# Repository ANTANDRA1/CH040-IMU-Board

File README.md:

ПЛАТА ДЛЯ IMU CH040

ОПИС ПРОЄКТУ

Проєкт являє собою односторонню друковану плату для підключення інерціального модуля CH040 IMU/VRU.

Плата розроблена в KiCad 10.

Основні завдання плати:

- встановлення модуля CH040;
- виведення всіх 18 контактів CH040 на гребінки Dupont з кроком 2.54 мм;
- додаткове виведення робочих інформаційних сигналів на роз'єм JST GH з кроком 1.25 мм;
- забезпечення живлення модуля;
- захист лінії живлення;
- монтажні отвори під гвинти М2.

CH040

CH040 — інерціальний модуль IMU/VRU.

Модуль підтримує UART та CAN-інтерфейси.

Для використання повноцінної CAN-шини необхідний зовнішній CAN-трансивер, оскільки CAN_TX та CAN_RX є логічними сигналами модуля, а не безпосередньо CANH та CANL.

Габарити модуля:

25 × 20 × 2.7 мм

РОЗ'ЄМ J1 — DUPONT 1×9, 2.54 ММ

1 — VDD
2 — GND
3 — EN
4 — IO1
5 — IO2
6 — RXD2
7 — TXD2
8 — GND
9 — IO5

РОЗ'ЄМ J2 — DUPONT 1×9, 2.54 ММ

1 — NRST
2 — RXD3
3 — TXD3
4 — CAN_TX
5 — CAN_RX
6 — IO9
7 — RXD1
8 — TXD1
9 — IO6

Таким чином, на J1 та J2 виведені всі 18 контактів CH040.

РОЗ'ЄМ J3 — JST GH 1×10, 1.25 ММ

На роз'єм J3 виведені робочі інформаційні та керуючі сигнали.

1 — EN
2 — IO1_EXT
3 — IO2_EXT
4 — IO5
5 — IO6
6 — UART1_TX
7 — UART1_RX
8 — CAN_TX
9 — CAN_RX
10 — NRST_EXT

Лінії IO1, IO2, TXD1, RXD1 та NRST підключені до J3 через послідовні резистори 1 кОм.

Контакти RXD2, TXD2, RXD3 та TXD3 не використовуються в поточній конфігурації CH040, а IO9 є зарезервованим, тому вони не дублюються на JST.

ЖИВЛЕННЯ

Живлення плати подається через роз'єм J4.

Робоча напруга:

3.3–5 В

Для захисту лінії живлення використані:

F1 — запобіжник 300 мА
D1 — TVS-діод SMF5.0CA

Схема живлення:

J4 → F1 → VDD → CH040

TVS-діод D1 підключений між VDD та GND.

ПЕРЕМИЧКА GND

Плата виконана односторонньою.

Контакт 8 модуля CH040 є контактом GND.

Через особливості одностороннього трасування його підключення до основної землі виконується через перемичку:

R6 — 0 Ом

Використовується вивідний THT-резистор, який фізично виконує функцію перемички над сигнальними доріжками.

ПОСАДКОВЕ МІСЦЕ CH040

Посадкове місце CH040 створене вручну відповідно до документації виробника.

Основні параметри:

габарит модуля — 25 × 20 мм
розмір контактної площадки — 1.4 × 1.2 мм
основний крок контактів — 2 мм

Під модулем створена спеціальна Keepout-зона.

У цій зоні заборонено:

- прокладати доріжки;
- розміщувати перехідні отвори;
- виконувати заливку міддю.

МОНТАЖ

На платі передбачено чотири монтажні отвори:

H1
H2
H3
H4

Отвори призначені для кріплення плати гвинтами М2.

ОСНОВНІ КОМПОНЕНТИ

U1 — CH040

J1, J2 — Dupont 1×9, 2.54 мм

J3 — JST GH 1×10, 1.25 мм

J4 — роз'єм живлення

R1–R5 — 1 кОм, корпус 0402

R6 — 0 Ом, THT

F1 — 300 мА

D1 — SMF5.0CA

H1–H4 — монтажні отвори М2

СТРУКТУРА ПРОЄКТУ

CH040

KiCad
    Ch040.kicad_pro
    Ch040.kicad_sch
    Ch040.kicad_pcb
    бібліотека символу CH040
    бібліотека посадкового місця CH040

Gerber & Drill
    Gerber-файли
    Drill-файли

Datasheet
    документація CH040

README.txt

ВІДТВОРЕННЯ ПРОЄКТУ

Для відкриття та редагування проєкту рекомендується використовувати KiCad 10.

1. Завантажити або клонувати репозиторій.

2. Відкрити файл Ch040.kicad_pro.

3. Перевірити підключення бібліотеки символу CH040 та бібліотеки його посадкового місця.

4. Відкрити принципову схему.

5. Відкрити PCB.

6. Запустити ERC для перевірки електричної схеми.

7. Запустити DRC для перевірки друкованої плати.

8. Для виробництва використовувати Gerber та Drill-файли з відповідної папки.

ПЕРЕВІРКА ПЛАТИ

Перед формуванням виробничих файлів виконано:

- ERC;
- DRC;
- перевірку нез'єднаних мереж;
- перевірку Keepout-зони CH040;
- перевірку плати у 3D Viewer;
- формування Gerber-файлів;
- формування Drill-файлів.

ПРИМІТКА

Проєкт виконаний відповідно до технічного завдання на розробку плати для IMU CH040.

Репозиторій містить принципову схему, PCB, користувацькі бібліотеки, Gerber-файли, файли свердління та документацію, необхідну для відтворення плати.

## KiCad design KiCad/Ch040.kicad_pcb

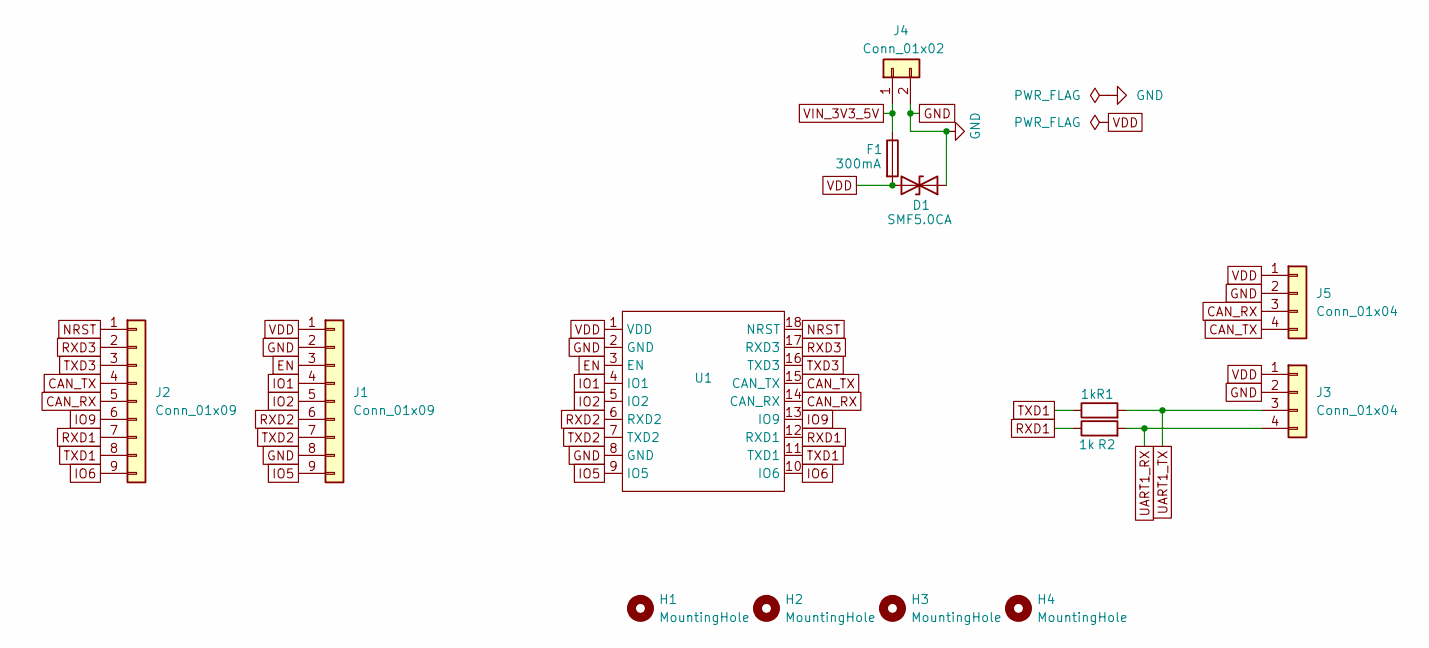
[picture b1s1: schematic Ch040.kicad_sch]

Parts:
D1: SMF5.0CA; D_SMA
F1: 300mA; Fuse_0603_1608Metric
H1, H2, H3, H4: MountingHole; MountingHole_2.2mm_M2
J1, J2: Conn_01x09; PinHeader_1x09_P2.54mm_Vertical
J3, J5: Conn_01x04; JST_GH_SM04B-GHS-TB_1x04-1MP_P1.25mm_Horizontal
J4: Conn_01x02; PinSocket_1x02_P2.54mm_Vertical
R1, R2: 1k; R_0805_2012Metric
U1: CH040

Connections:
CAN_RX: J2.5, J5.3, U1.14 (CAN_RX)
CAN_TX: J2.4, J5.4, U1.15 (CAN_TX)
EN: J1.3, U1.3 (EN)
GND: D1.1 (A1), J1.2, J1.8, J3.2, J4.2, J5.2, U1.2 (GND), U1.8 (GND)
IO1: J1.4, U1.4 (IO1)
IO2: J1.5, U1.5 (IO2)
IO5: J1.9, U1.9 (IO5)
IO6: J2.9, U1.10 (IO6)
IO9: J2.6, U1.13 (IO9)
NRST: J2.1, U1.18 (NRST)
RXD1: J2.7, R2.1, U1.12 (RXD1)
RXD2: J1.6, U1.6 (RXD2)
RXD3: J2.2, U1.17 (RXD3)
TXD1: J2.8, R1.1, U1.11 (TXD1)
TXD2: J1.7, U1.7 (TXD2)
TXD3: J2.3, U1.16 (TXD3)
UART1_RX: J3.4, R2.2
UART1_TX: J3.3, R1.2
VDD: D1.2 (A2), F1.2, J1.1, J3.1, J5.1, U1.1 (VDD)
VIN_3V3_5V: F1.1, J4.1

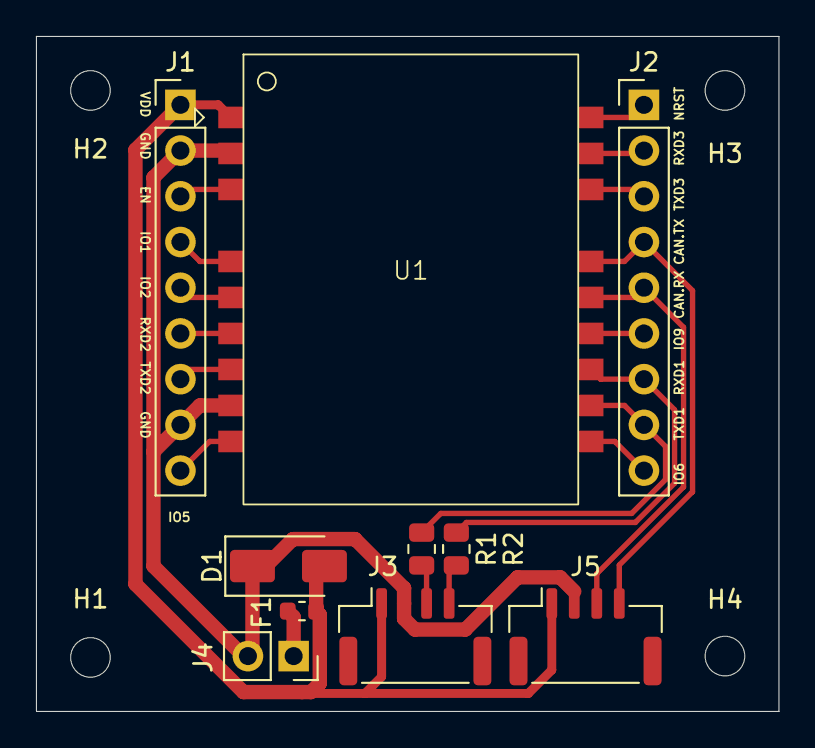
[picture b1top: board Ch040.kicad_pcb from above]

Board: 2 copper layers, 41.2 x 37.5 mm, 14 parts (0 on the bottom side), 20 nets.
